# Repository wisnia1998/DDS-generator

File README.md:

# DDS-generator
DDS generator based on Adruino board and AD9850 for PUE student classes

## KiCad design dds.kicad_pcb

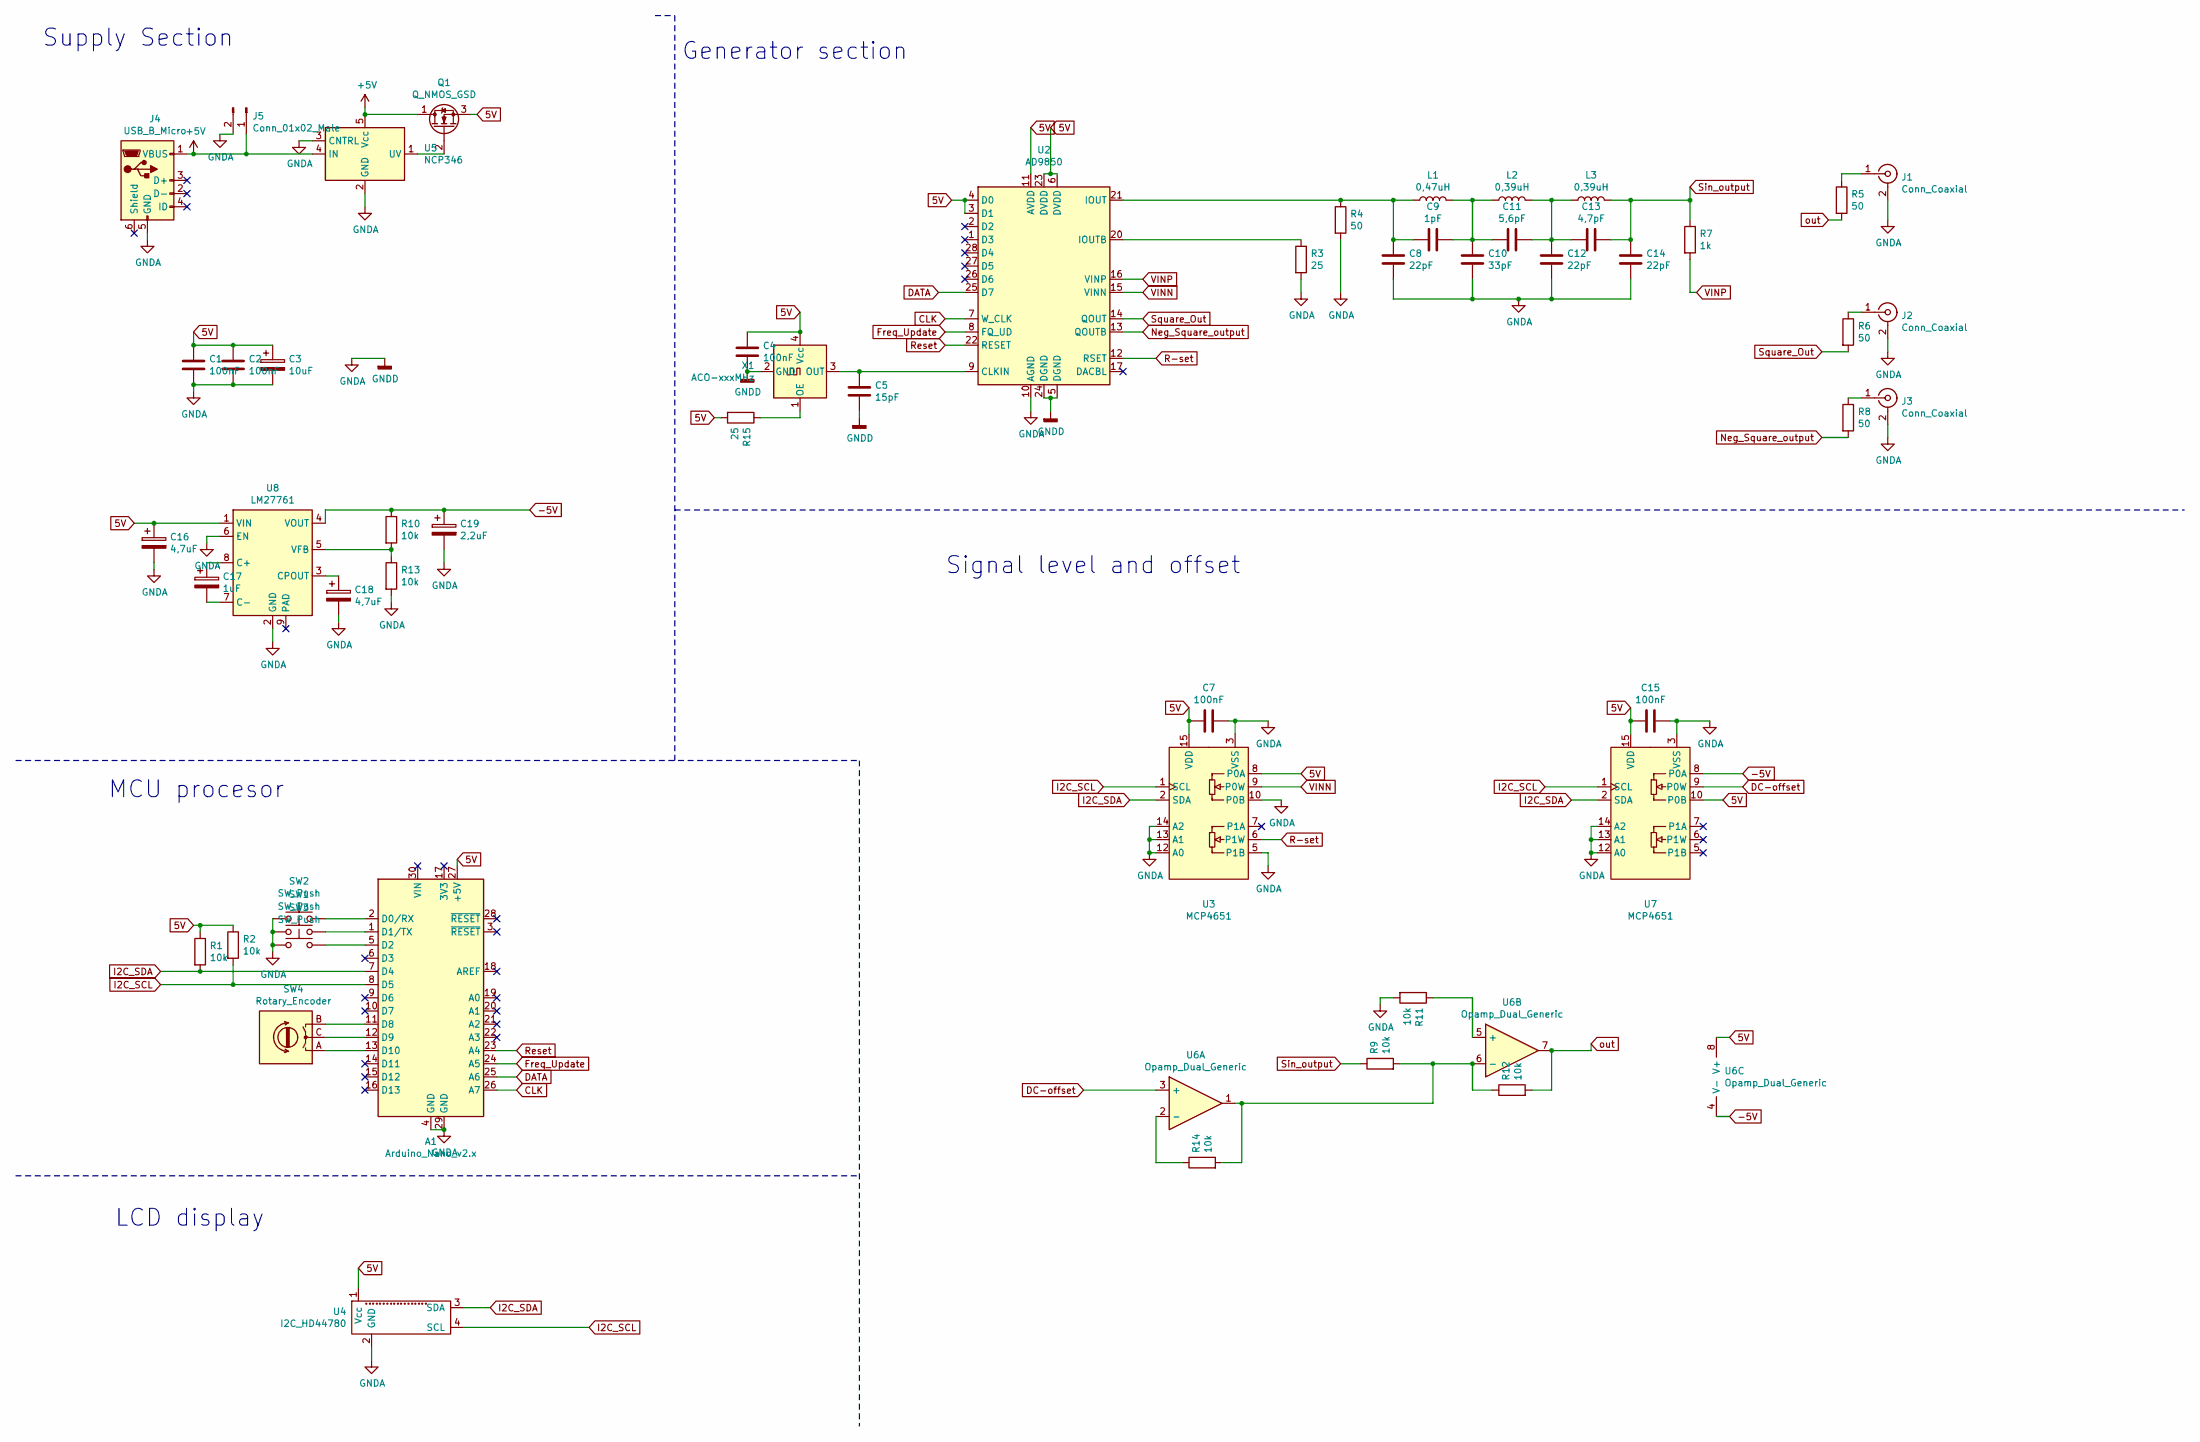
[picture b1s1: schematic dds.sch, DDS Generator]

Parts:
A1: Arduino_Nano_v2.x; Arduino_Nano
C1, C2, C4, C7, C15: 100nF; C_0805_2012Metric_Pad1.15x1.40mm_HandSolder
C3: 10uF; C_Elec_8x6.2
C5: 15pF; C_0805_2012Metric_Pad1.15x1.40mm_HandSolder
C8, C12, C14: 22pF; C_0805_2012Metric_Pad1.15x1.40mm_HandSolder
C9: 1pF; C_0805_2012Metric_Pad1.15x1.40mm_HandSolder
C10: 33pF; C_0805_2012Metric_Pad1.15x1.40mm_HandSolder
C11: 5,6pF; C_0805_2012Metric_Pad1.15x1.40mm_HandSolder
C13: 4,7pF; C_0805_2012Metric_Pad1.15x1.40mm_HandSolder
C16, C18: 4,7uF; C_Elec_8x6.2
C17: 1uF; C_Elec_8x6.2
C19: 2,2uF; C_Elec_8x6.2
J1, J2, J3: Conn_Coaxial; BNC_TEConnectivity_1478204_Vertical
J4: USB_B_Micro; USB_Micro-B_Wuerth_629105150521
J5: Conn_01x02_Male; PinHeader_1x02_P1.00mm_Vertical
L1: 0,47uH; L_1206_3216Metric_Pad1.42x1.75mm_HandSolder
L2, L3: 0,39uH; L_1206_3216Metric_Pad1.42x1.75mm_HandSolder
Q1: Q_NMOS_GSD; TO-252-3_TabPin4
R1, R2, R9, R10, R11, R12, R13, R14: 10k; R_0805_2012Metric_Pad1.15x1.40mm_HandSolder
R3, R15: 25; R_0805_2012Metric_Pad1.15x1.40mm_HandSolder
R4, R5, R6, R8: 50; R_0805_2012Metric_Pad1.15x1.40mm_HandSolder
R7: 1k; R_0805_2012Metric_Pad1.15x1.40mm_HandSolder
SW1, SW2, SW3: SW_Push; SW_PUSH_6mm
SW4: Rotary_Encoder; RotaryEncoder_Alps_EC12E_Vertical_H20mm
U2: AD9850; SSOP-28_5.3x10.2mm_P0.65mm
U3, U7: MCP4651; QFN-16-1EP_4x4mm_P0.65mm_EP2.5x2.5mm
U4: I2C_HD44780; PinHeader_1x18_P1.00mm_Vertical
U5: NCP346; SOT-23-6
U6: Opamp_Dual_Generic; HSOP-8-1EP_3.9x4.9mm_P1.27mm_EP2.41x3.1mm
U8: LM27761; WSON-8-1EP_2x2mm_P0.5mm_EP0.9x1.6mm
X1: ACO-xxxMHz; Oscillator_SMD_TXC_7C-4Pin_5.0x3.2mm

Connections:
5V: A1.27 (+5V), C1.1, C2.1, C3.1, C4.1, C7.1, C15.1, C16.1, Q1.3 (S), R1.1, R2.1, R15.2, U2.3 (D1), U2.4 (D0), U2.6 (DVDD), U2.11 (AVDD), U2.18 (AVDD), U2.23 (DVDD), U3.8 (P0A), U3.15 (VDD), U4.1 (Vcc), U6.8 (V+), U7.10 (P0B), U7.15 (VDD), U8.1 (VIN), X1.4 (Vcc)
+5V: J4.1 (VBUS), J5.1, Q1.1 (D), U5.4 (IN), U5.5 (Vcc)
-5V: C19.1, R10.1, U6.4 (V-), U7.8 (P0A), U8.4 (VOUT)
CLK: A1.26 (A7), U2.7 (W_CLK)
DATA: A1.25 (A6), U2.25 (D7)
DC-offset: U6.3 (+), U7.9 (P0W)
Freq_Update: A1.24 (A5), U2.8 (FQ_UD)
I2C_SCL: A1.8 (D5), R2.2, U3.1 (SCL), U4.4 (SCL), U7.1 (SCL)
I2C_SDA: A1.7 (D4), R1.2, U3.2 (SDA), U4.3 (SDA), U7.2 (SDA)
Neg_Square_output: R8.2, U2.13 (QOUTB)
unnamed: A1.1 (D1/TX), SW1.2
unnamed: A1.2 (D0/RX), SW2.2
unnamed: A1.5 (D2), SW3.2
unnamed: A1.11 (D8), SW4.B
unnamed: A1.12 (D9), SW4.C
unnamed: A1.13 (D10), SW4.A
unnamed: C5.1, U2.9 (CLKIN), X1.3 (OUT)
unnamed: C8.1, C9.1, L1.1, R4.1, U2.21 (IOUT)
unnamed: C9.2, C10.1, C11.2, L1.2, L2.1
unnamed: C11.1, C12.2, C13.2, L2.2, L3.1
unnamed: C17.1, U8.8 (C+)
unnamed: C17.2, U8.7 (C-)
unnamed: C18.1, U8.3 (CPOUT)
unnamed: J1.1 (In), R5.1
unnamed: J2.1 (In), R6.1
unnamed: J3.1 (In), R8.1
unnamed: Q1.2 (G), U5.1 (UV)
unnamed: R3.1, U2.20 (IOUTB)
unnamed: R10.2, R13.1, U8.5 (VFB)
unnamed: R11.1, U6.5 (+)
unnamed: R9.2, R12.1, R14.2, U6.1, U6.6 (-)
unnamed: R14.1, U6.2 (-)
unnamed: R15.1, X1.1 (OE)
R-set: U2.12 (RSET), U3.6 (P1W)
Reset: A1.23 (A4), U2.22 (RESET)
Sin_output: C13.1, C14.1, L3.2, R7.1, R9.1
Square_Out: R6.2, U2.14 (QOUT)
VINN: U2.15 (VINN), U3.9 (P0W)
VINP: R7.2, U2.16 (VINP)
out: R5.2, R12.2, U6.7

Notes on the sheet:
Supply Section
Generator section
MCU procesor
LCD display
Signal level and offset

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
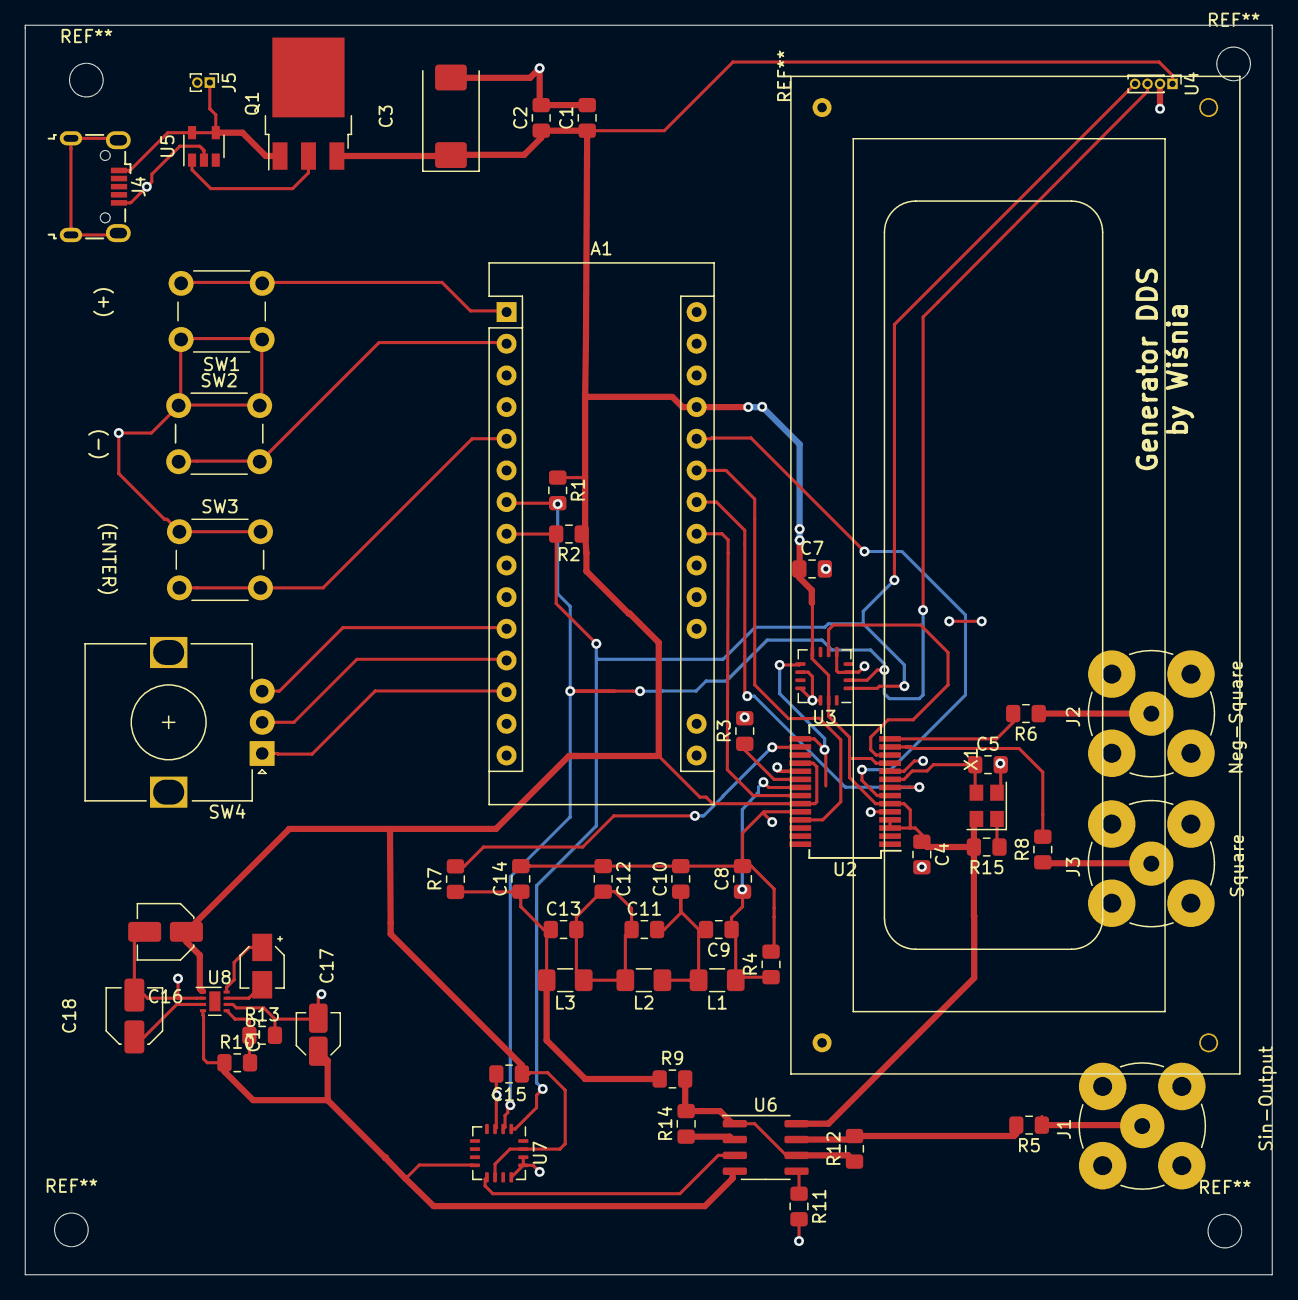
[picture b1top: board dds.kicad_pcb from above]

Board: 2 copper layers, 100.0 x 100.2 mm, 55 parts (0 on the bottom side), 41 nets.

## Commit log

2020-10-13 add files
